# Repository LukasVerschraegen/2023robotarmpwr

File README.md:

# 2023robotarmpwr

Doelstelling:
ontwerpen en programmeren van een robotarm. En het ontwerpen yan dels stüring voor de steppermotoren
Het
op basis van een micro controlletalie draadloos kan bediend worden. En eventueel een extra display kan worden
toegevoegd ter visualisatie van de instelbare parameters.
De robot zal een automatisatierobot zijn die éénmalig wordt ingesteld en zo repetitive taken kan uitvoeren. Je kan
verschillende taken en cyclussen aanmaken die dan kunnen worden geselecteerd uit het menu op het display. Het
instellen van een cyclus kan handmatig gebeuren via het display, of via code.De volledige constructie van de
robot zal worden uitgewerkt met de 3D-printer,

Verplichte onderdelen rapport:

Kaft (voorblad)                                                                                              (gebruik de recentste logo's)
Abstract (in het Engels en informatief)
Inhoudsopgave                                                                                             
Codefragmentenlijst                                                                                           
Figurenlijst
Tabellenlijst
Afkortingenlijst
Inleiding                                                                                                        
1 Hoofdstuktitel                                                                                             
2 ...                                                                                                                 
3 ...
4 ...                                                                       
Conclusie
Handleiding   (enkel verplicht indien laboproeven moeten geschreven worden, dan horen ze hier / indien het project in gebruik genomen zal worden, schrijf dan een handleiding)
Literatuurlijst
Bijlagenoverzicht  (opmaak zoals inhoudsopgave)
Bijlage 1: Kopieën datasheets
Bijlage 2: Vergaderverslagen
Bijlage 3:  Logboek rapporteren

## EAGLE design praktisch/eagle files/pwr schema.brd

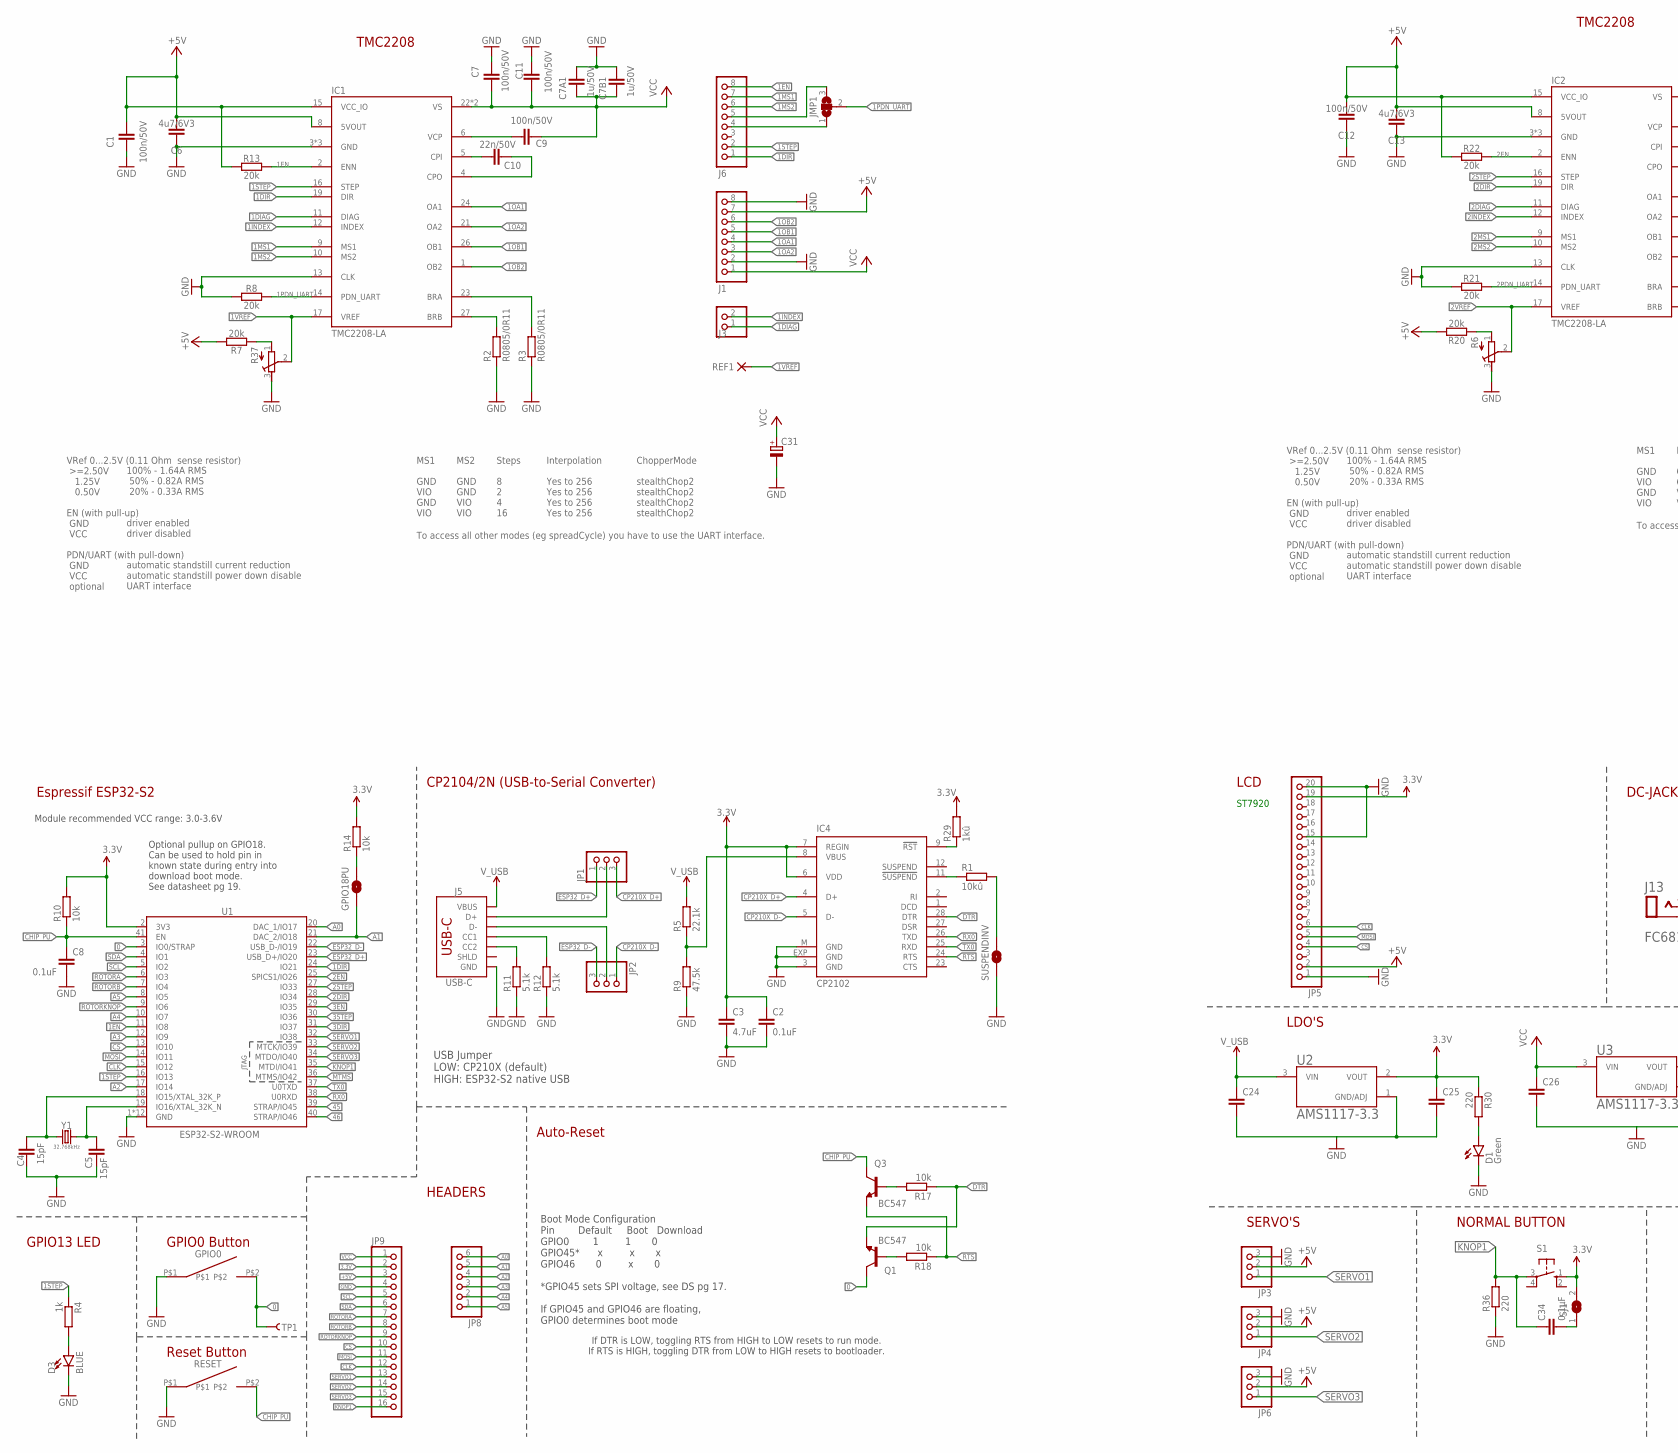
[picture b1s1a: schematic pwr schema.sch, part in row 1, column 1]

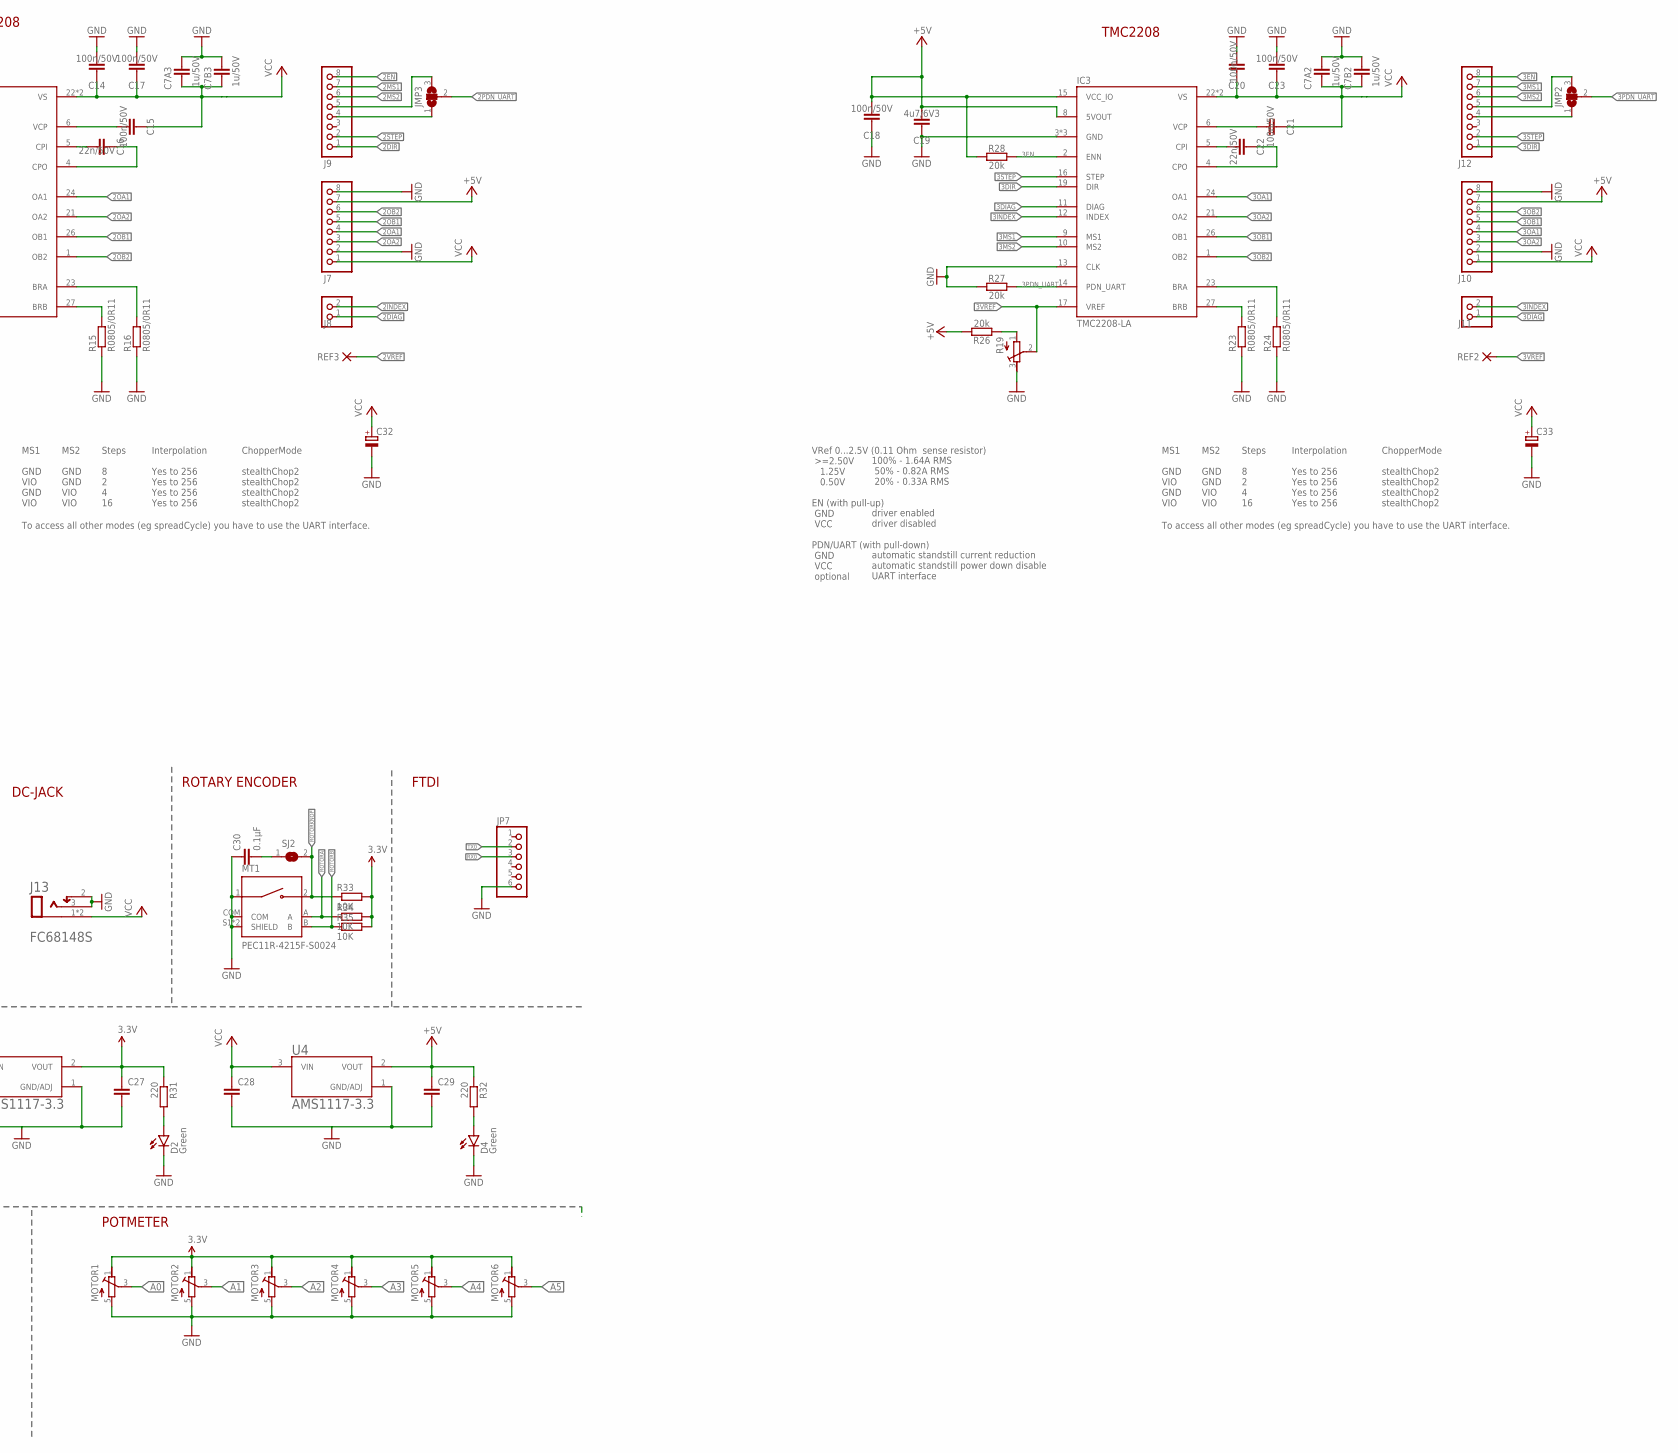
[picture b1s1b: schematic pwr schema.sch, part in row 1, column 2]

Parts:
C1, C7, C9, C11, C12, C14, C15, C17, C18, C20, C21, C23: 100n/50V; C1206
C2, C8: 0.1uF; C1206
C3: 4.7uF; C1206
C4, C5: 15pF; C1206
C6, C13, C19: 4u7/6V3; C1206
C7A1, C7A2, C7A3, C7B1, C7B2, C7B3: 1u/50V; C1206
C10, C16, C22: 22n/50V; C1206
C24, C25, C26, C27, C28, C29: C-EUC1206; C1206
C30, C34: 0.1µF; C1206
C31, C32, C33: CPOL-EUE2.5-6; E2,5-6
D1, D2, D4: Green; CHIP-LED0603
D3: BLUE; LED-0603
GPIO0: SWITCHSMD3X6MM
GPIO18PU: JUMPER-SMT_2_NO_SILK; SMT-JUMPER_2_NO_SILK
IC1, IC2, IC3: TMC2208-LA; QFN28-PAD
IC4: CP2102; MLP28
J1, J6, J7, J9, J10, J12: PINHD-1X8; 1X08
J3, J8, J11: PINHD-1X2; 1X02
J5: USB-C; USB-C-16P-4LAYER-ISOLATED
J13: CLIFF_FC68148SCLIFF_FC68148S_0_0; CLIFF_FC68148S_0
JMP1, JMP2, JMP3: JUMPER3-0402-NC; JUMPER3-0402_NC
JP1, JP2, JP3, JP4, JP6: PINHD-1X3; 1X03
JP5: PINHD-1X20; 1X20
JP7, JP8: PINHD-1X6; 1X06
JP9: PINHD-1X16; 1X16
MOTOR1, MOTOR2, MOTOR3, MOTOR4, MOTOR5, MOTOR6: POTMETER
MT1: PEC11R-4215F-S0024; XDCR_PEC11R-4215F-S0024
Q1, Q3: BC547; TO92
R1: 10kû; R1206
R2, R3, R15, R16, R23, R24: R0805/0R11; R1206
R4: 1k; R1206
R5: 22.1k; R1206
R6, R19, R37: R-TRIMM3103; RTRIM3103
R7, R8, R13, R20, R21, R22, R26, R27, R28: 20k; R1206
R9: 47.5k; R1206
R10, R14, R17, R18: 10k; R1206
R11, R12: 5.1k; R1206
R29: 1kû; R1206
R30, R31, R32, R36: 220; R1206
R33, R34, R35: 10K; R1206
REF1, REF2, REF3: PAD-0.6-1.1
RESET: SWITCHSMD3X6MM
S1: 10-XX; B3F-10XX
SJ1, SJ2: SJ
SUSPENDINV: JUMPER-SMT_2_NO_SILK; SMT-JUMPER_2_NO_SILK
TP1: TEST-POINTTP_15TH_THRU; TP_15TH
U1: ESP32-S2-WROOM
U2, U3, U4: AMS1117-3.3; SOT229P700X180-4N
Y1: 32.768kHz; CRYSTAL-SMD-3.2X1.5MM

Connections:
0: GPIO0.P$2, Q1.3 (C), TP1.P$1, U1.3 (IO0/STRAP)
1BRA: IC1.23 (BRA), R3.2
1BRB: IC1.27 (BRB), R2.2
1CPI: C10.2, IC1.5 (CPI)
1CPO: C10.1, IC1.4 (CPO)
1DIAG: IC1.11 (DIAG), J3.1
1DIR: IC1.19 (DIR), J6.1, U1.24 (IO21)
1EN: IC1.2 (ENN), J6.8, R13.2, U1.11 (IO8)
1INDEX: IC1.12 (INDEX), J3.2
1MS1: IC1.9 (MS1), J6.7
1MS2: IC1.10 (MS2), J6.6
1OA1: IC1.24 (OA1), J1.4
1OA2: IC1.21 (OA2), J1.3
1OB1: IC1.26 (OB1), J1.5
1OB2: IC1.1 (OB2), J1.6
1PDN_UART: IC1.14 (PDN_UART), JMP1.2, R8.2
1STEP: IC1.16 (STEP), J6.2, R4.1, U1.16 (IO13)
1VCP: C9.2, IC1.6 (VCP)
1VREF: IC1.17 (VREF), R37.2 (S), REF1.1
1VREF1: R7.1, R37.1 (A)
2BRA: IC2.23 (BRA), R16.2
2BRB: IC2.27 (BRB), R15.2
2CPI: C16.2, IC2.5 (CPI)
2CPO: C16.1, IC2.4 (CPO)
2DIAG: IC2.11 (DIAG), J8.1
2DIR: IC2.19 (DIR), J9.1, U1.28 (IO34)
2EN: IC2.2 (ENN), J9.8, R22.2, U1.25 (SPICS1/IO26)
2INDEX: IC2.12 (INDEX), J8.2
2MS1: IC2.9 (MS1), J9.7
2MS2: IC2.10 (MS2), J9.6
2OA1: IC2.24 (OA1), J7.4
2OA2: IC2.21 (OA2), J7.3
2OB1: IC2.26 (OB1), J7.5
2OB2: IC2.1 (OB2), J7.6
2PDN_UART: IC2.14 (PDN_UART), JMP3.2, R21.2
2STEP: IC2.16 (STEP), J9.2, U1.27 (IO33)
2VCP: C15.2, IC2.6 (VCP)
2VREF: IC2.17 (VREF), R6.2 (S), REF3.1
2VREF1: R6.1 (A), R20.1
3.3V: C2.1, C3.1, C25.1, C27.1, IC4.6 (VDD), IC4.7 (REGIN), JP5.19, JP9.2, MOTOR1.1 (E), MOTOR2.1 (E), MOTOR3.1 (E), MOTOR4.1 (E), MOTOR5.1 (E), MOTOR6.1 (E), R10.2, R14.2, R29.2, R30.1, R31.1, R33.2, R34.2, R35.2, S1.1 (S), SJ1.2, U1.2 (3V3), U2.2 (VOUT), U3.2 (VOUT)
3BRA: IC3.23 (BRA), R24.2
3BRB: IC3.27 (BRB), R23.2
3CPI: C22.2, IC3.5 (CPI)
3CPO: C22.1, IC3.4 (CPO)
3DIAG: IC3.11 (DIAG), J11.1
3DIR: IC3.19 (DIR), J12.1, U1.31 (IO37)
3EN: IC3.2 (ENN), J12.8, R28.2, U1.29 (IO35)
3INDEX: IC3.12 (INDEX), J11.2
3MS1: IC3.9 (MS1), J12.7
3MS2: IC3.10 (MS2), J12.6
3OA1: IC3.24 (OA1), J10.4
3OA2: IC3.21 (OA2), J10.3
3OB1: IC3.26 (OB1), J10.5
3OB2: IC3.1 (OB2), J10.6
3PDN_UART: IC3.14 (PDN_UART), JMP2.2, R27.2
3STEP: IC3.16 (STEP), J12.2, U1.30 (IO36)
3VCP: C21.2, IC3.6 (VCP)
3VREF: IC3.17 (VREF), R19.2 (S), REF2.1
3VREF1: R19.1 (A), R26.1
45: U1.39 (STRAP/IO45)
46: U1.40 (STRAP/IO46)
+5V: C1.2, C6.2, C12.2, C13.2, C18.2, C19.2, C29.1, IC1.8 (5VOUT), IC1.15 (VCC_IO), IC2.8 (5VOUT), IC2.15 (VCC_IO), IC3.8 (5VOUT), IC3.15 (VCC_IO), J1.7, J7.7, J10.7, JP3.2, JP4.2, JP5.2, JP6.2, JP9.3, R7.2, R13.1, R20.2, R22.1, R26.2, R28.1, R32.1, U4.2 (VOUT)
A0: JP8.6, MOTOR1.3 (S), U1.20 (DAC_1/IO17)
A1: GPIO18PU.1, JP8.5, MOTOR2.3 (S), U1.21 (DAC_2/IO18)
A2: JP8.4, MOTOR3.3 (S), U1.17 (IO14)
A3: JP8.3, MOTOR4.3 (S), U1.12 (IO9)
A4: JP8.2, MOTOR5.3 (S), U1.10 (IO7)
A5: JP8.1, MOTOR6.3 (S), U1.8 (IO5)
CC1: J5.A5 (CC1), R12.2
CC2: J5.B5 (CC2), R11.2
CHIP_PU: C8.1, Q3.3 (C), R10.1, RESET.P$2, U1.41 (EN)
CLK: JP5.6, JP9.12, U1.15 (IO12)
CP210X_D+: IC4.4 (D+), JP1.3
CP210X_D-: IC4.5 (D-), JP2.1
CS: JP5.4, JP9.10, U1.13 (IO10)
DTR: IC4.28 (DTR), Q1.1 (E), R17.1
ESP32_D+: JP1.1, U1.23 (USB_D+/IO20)
ESP32_D-: JP2.3, U1.22 (USB_D-/IO19)
GND: C1.1, C2.2, C3.2, C4.1, C5.1, C6.1, C7.2, C7A1.2, C7A2.2, C7A3.2, C7B1.2, C7B2.2, C7B3.2, C8.2, C11.2, C12.1, C13.1, C14.2, C17.2, C18.1, C19.1, C20.2, C23.2, C24.2, C25.2, C26.2, C27.2, C28.2, C29.2, C30.1, C31.-, C32.-, C33.-, D1.C, D2.C, D3.C, D4.C, GPIO0.P$1, IC1.3 (GND), IC1.13 (CLK), IC1.18 (GND), IC1.TP (GND), IC2.3 (GND), IC2.13 (CLK), IC2.18 (GND), IC2.TP (GND), IC3.3 (GND), IC3.13 (CLK), IC3.18 (GND), IC3.TP (GND), IC4.3 (GND), IC4.EXP (GND), IC4.M (GND), J1.2, J1.8, J5.GND, J5.GND2 (GND), J7.2, J7.8, J10.2, J10.8, J13.2, J13.3, JP3.3, JP4.3, JP5.1, JP5.15, JP5.20, JP6.3, JP7.6, JP9.4, MOTOR1.5 (A), MOTOR2.5 (A), MOTOR3.5 (A), MOTOR4.5 (A), MOTOR5.5 (A), MOTOR6.5 (A), MT1.1, MT1.COM, MT1.S1 (SHIELD), MT1.S2 (SHIELD), R2.1, R3.1, R6.3 (E), R8.1, R9.1, R11.1, R12.1, R15.1, R16.1, R19.3 (E), R21.1, R23.1, R24.1, R27.1, R36.1, R37.3 (E), RESET.P$1, SUSPENDINV.1, U1.1 (GND), U1.26 (GND), U1.42 (GND), U1.GNDEP0 (GND), U1.GNDEP1 (GND), U1.GNDEP2 (GND), U1.GNDEP3 (GND), U1.GNDEP4 (GND), U1.GNDEP5 (GND), U1.GNDEP6 (GND), U1.GNDEP7 (GND), U1.GNDEP8 (GND), U2.1 (GND/ADJ), U3.1 (GND/ADJ), U4.1 (GND/ADJ)
KNOP1: C34.1, JP9.16, R36.2, S1.3, U1.35 (MTDI/IO41)
MOSI: JP5.5, JP9.11, U1.14 (IO11)
MTMS: U1.36 (MTMS/IO42)
unnamed: IC4.11 (!SUSPEND), R1.1
unnamed: D3.A, R4.2
unnamed: J5.A6 (D+), J5.B6 (D+), JP1.2
unnamed: IC4.8 (VBUS), R5.1, R9.2
unnamed: J5.A7 (D-), J5.B7 (D-), JP2.2
unnamed: C4.2, U1.18 (IO15/XTAL_32K_P), Y1.P$1 (1)
unnamed: C5.2, U1.19 (IO16/XTAL_32K_N), Y1.P$2 (2)
unnamed: J6.4, JMP1.1
unnamed: Q3.2 (B), R17.2
unnamed: J6.5, JMP1.3
unnamed: Q1.2 (B), R18.2
unnamed: J9.4, JMP3.1
unnamed: GPIO18PU.2, R14.1
unnamed: J9.5, JMP3.3
unnamed: J12.4, JMP2.1
unnamed: J12.5, JMP2.3
unnamed: IC4.9 (!RST), R29.1
unnamed: R1.2, SUSPENDINV.2
unnamed: D1.A, R30.2
unnamed: D2.A, R31.2
unnamed: D4.A, R32.2
NCKNOP: C34.2, SJ1.1
NCROTORY: C30.2, SJ2.1
ROTORA: JP9.7, MT1.A, R34.1, U1.6 (IO3)
ROTORB: JP9.8, MT1.B, R35.1, U1.7 (IO4)
ROTORKNOP: JP9.9, MT1.2, R33.1, SJ2.2, U1.9 (IO6)
RTS: IC4.24 (RTS), Q3.1 (E), R18.1
RX0: IC4.26 (TXD), JP7.3, U1.38 (U0RXD)
SCL: JP9.5, U1.5 (IO2)
SDA: JP9.6, U1.4 (IO1)
SERVO1: JP3.1, JP9.13, U1.32 (IO38)
SERVO2: JP4.1, JP9.14, U1.33 (MTCK/IO39)
SERVO3: JP6.1, JP9.15, U1.34 (MTDO/IO40)
TX0: IC4.25 (RXD), JP7.2, U1.37 (U0TXD)
VCC: C7.1, C7A1.1, C7A2.1, C7A3.1, C7B1.1, C7B2.1, C7B3.1, C9.1, C11.1, C14.1, C15.1, C17.1, C20.1, C21.1, C23.1, C26.1, C28.1, C31.+, C32.+, C33.+, IC1.22 (VS), IC1.28 (VS), IC2.22 (VS), IC2.28 (VS), IC3.22 (VS), IC3.28 (VS), J1.1, J7.1, J10.1, J13.1, J13.1-2 (1), JP9.1, U3.3 (VIN), U4.3 (VIN)
V_USB: C24.1, J5.VBUS1 (VBUS), J5.VBUS2 (VBUS), R5.2, U2.3 (VIN)

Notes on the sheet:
Espressif ESP32-S2
Module recommended VCC range: 3.0-3.6V
Optional pullup on GPIO18. Can be used to hold pin in known state during entry into download boot mode. See datasheet pg 19.
CP2104/2N (USB-to-Serial Converter)
USB Jumper LOW: CP210X (default) HIGH: ESP32-S2 native USB
GPIO13 LED
Reset Button
GPIO0 Button
Boot Mode Configuration Pin Default Boot Download GPIO0 1 1 0 GPIO45* x x x GPIO46 0 x 0 *GPIO45 sets SPI voltage, see DS pg 17. If GPIO45 and GPIO46 are floating, GPIO0 determines boot mode
Auto-Reset
If DTR is LOW, toggling RTS from HIGH to LOW resets to run mode. If RTS is HIGH, toggling DTR from LOW to HIGH resets to bootloader.
VRef 0...2.5V (0.11 Ohm sense resistor) >=2.50V 1.25V 0.50V EN (with pull-up) GND VCC PDN/UART (with pull-down) GND VCC optional
100% - 1.64A RMS 50% - 0.82A RMS 20% - 0.33A RMS driver enabled driver disabled automatic standstill current reduction automatic standstill power down disable UART interface
MS1 GND VIO GND VIO
MS2 GND GND VIO VIO
Steps 8 2 4 16
Interpolation Yes to 256 Yes to 256 Yes to 256 Yes to 256
ChopperMode stealthChop2 stealthChop2 stealthChop2 stealthChop2
To access all other modes (eg spreadCycle) you have to use the UART interface.
ST7920
HEADERS
LCD
DC-JACK
ROTARY ENCODER
FTDI
LDO'S
SERVO'S
NORMAL BUTTON
POTMETER
TMC2208

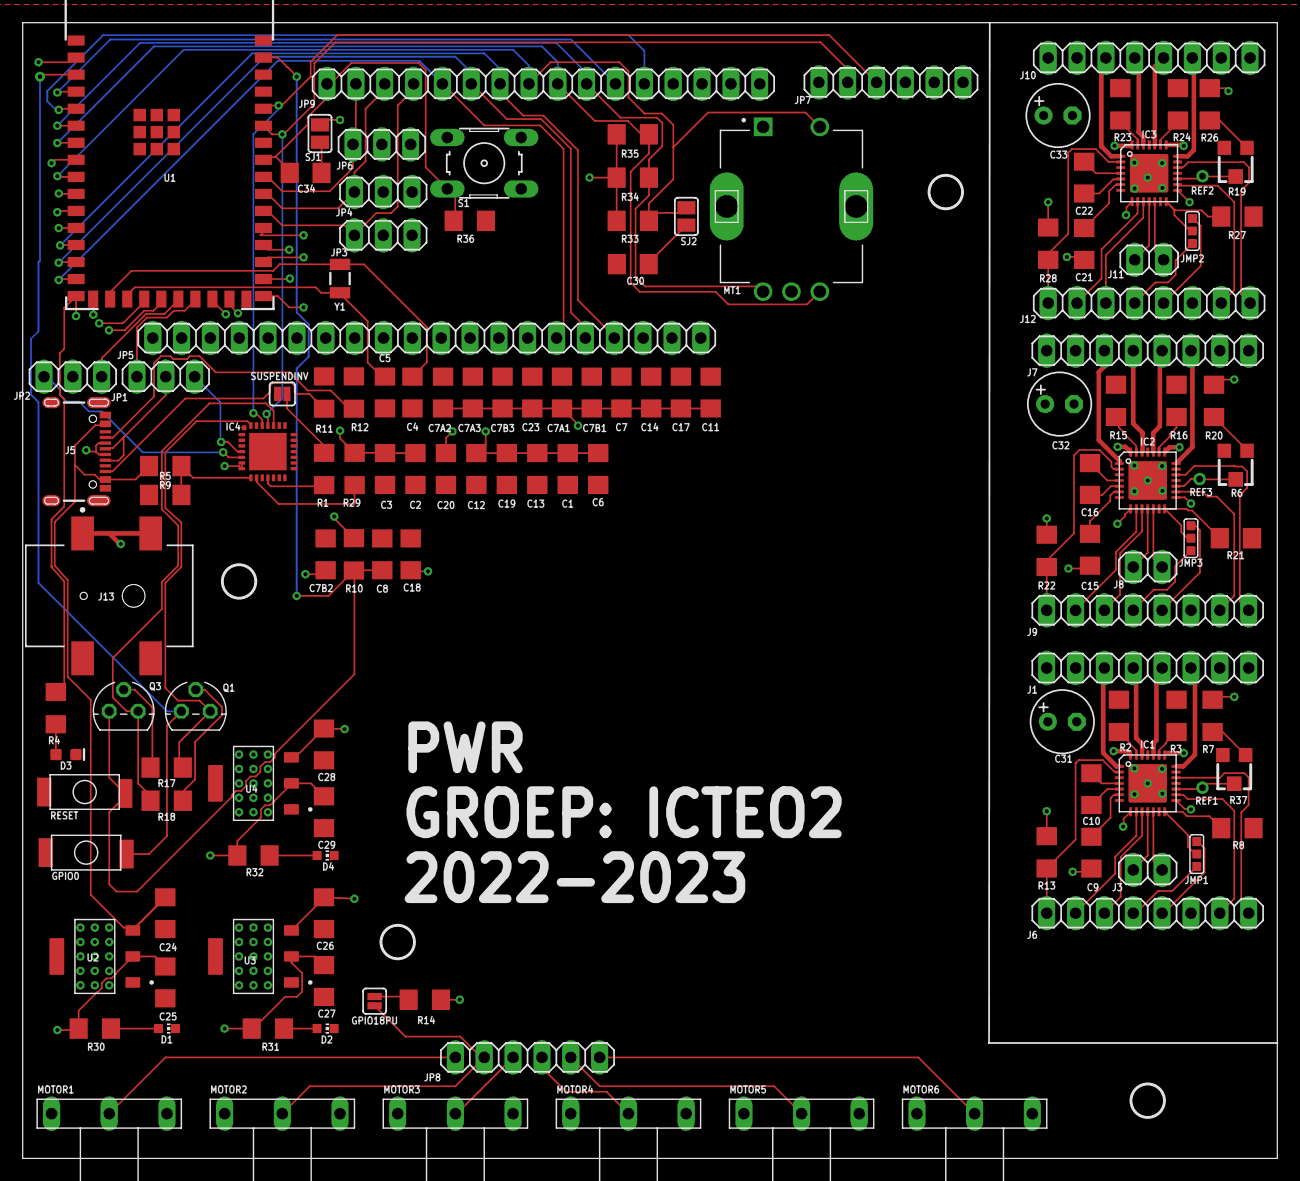
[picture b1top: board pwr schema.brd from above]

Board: 4 copper layers, 110.5 x 100.0 mm, 136 parts (0 on the bottom side), 115 nets.

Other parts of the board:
U$1, U$2, U$3, U$4: 2,8

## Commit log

2023-01-26 Create test
2023-01-26 Create logboek

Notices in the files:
parts and their libraries:
SparkFun-LED: Licensing: Creative Commons ShareAlike 4.0 International - https://creativecommons.org/licenses/by-sa/4.0
